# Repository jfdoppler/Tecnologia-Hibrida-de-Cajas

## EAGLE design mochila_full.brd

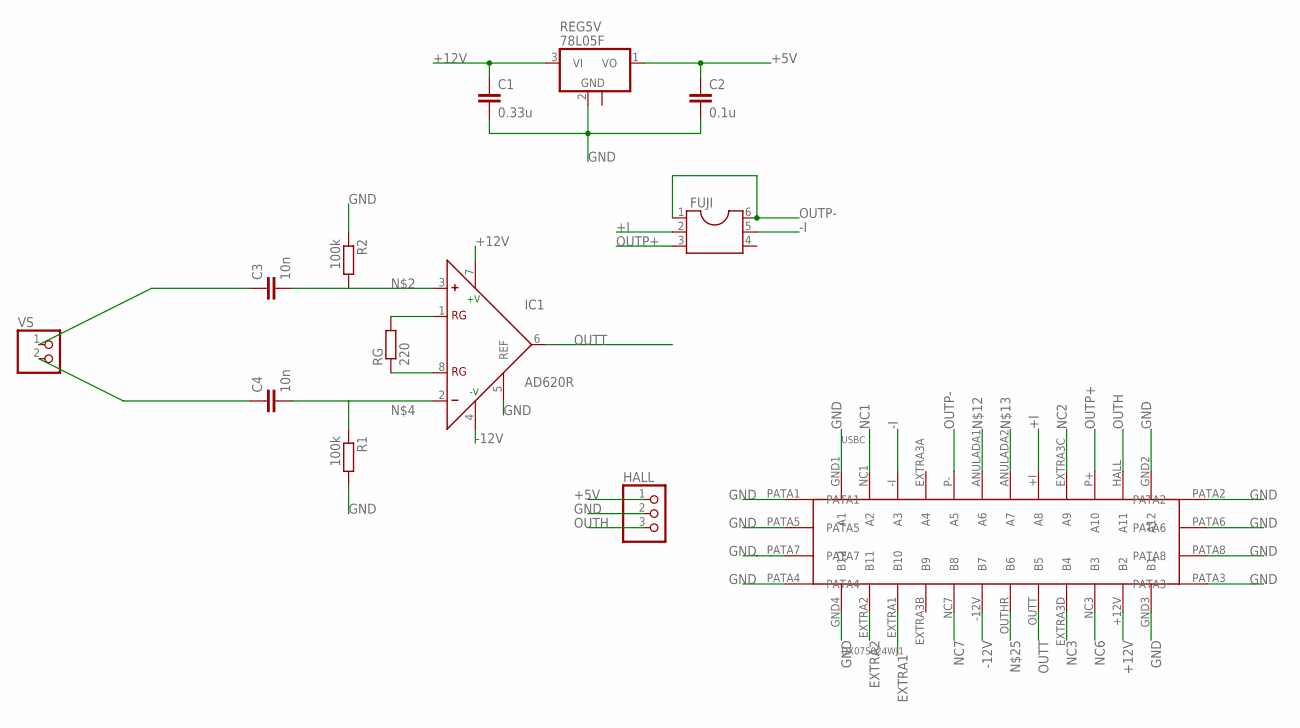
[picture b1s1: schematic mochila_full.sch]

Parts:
C1: 0.33u; C0805
C2: 0.1u; C0805
C3, C4: 10n; C0805
FUJI: DIL6; DIL06
HALL: PINHD-1X3; 1X03
IC1: AD620R; SO8
R1, R2: 100k; R0805
REG5V: 78L05F; SOT89
RG: 220; R0805
USBC: DX07S024WJ1
VS: PINHD-1X2; 1X02

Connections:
+5V: C2.1, HALL.1, REG5V.1 (VO)
+12V: C1.1, IC1.7 (+V), REG5V.3 (VI), USBC.+12V (B2)
+I: FUJI.2, USBC.+I (A8)
-12V: IC1.4 (-V), USBC.-12V (B7)
-I: FUJI.5, USBC.-I (A3)
EXTRA1: USBC.EXTRA1 (B10)
EXTRA2: USBC.EXTRA2 (B11)
GND: C1.2, C2.2, HALL.2, IC1.5 (REF), R1.2, R2.1, REG5V.2 (GND), USBC.GND1 (A1), USBC.GND2 (A12), USBC.GND3 (B1), USBC.GND4 (B12), USBC.PATA1, USBC.PATA2, USBC.PATA3, USBC.PATA4, USBC.PATA5, USBC.PATA6, USBC.PATA7, USBC.PATA8
unnamed: C3.1, VS.1
unnamed: C3.2, IC1.3 (+), R2.2
unnamed: C4.1, VS.2
unnamed: C4.2, IC1.2 (-), R1.1
unnamed: IC1.1 (RG), RG.2
unnamed: IC1.8 (RG), RG.1
NC1: USBC.NC1 (A2)
NC2: USBC.EXTRA3C (A9)
NC3: USBC.EXTRA3D (B4)
NC6: USBC.NC3 (B3)
NC7: USBC.NC7 (B8)
OUTH: HALL.3, USBC.HALL (A11)
OUTP+: FUJI.3, USBC.P+ (A10)
OUTP-: FUJI.1, FUJI.6, USBC.P- (A5)
OUTT: IC1.6 (OUT), USBC.OUTT (B5)

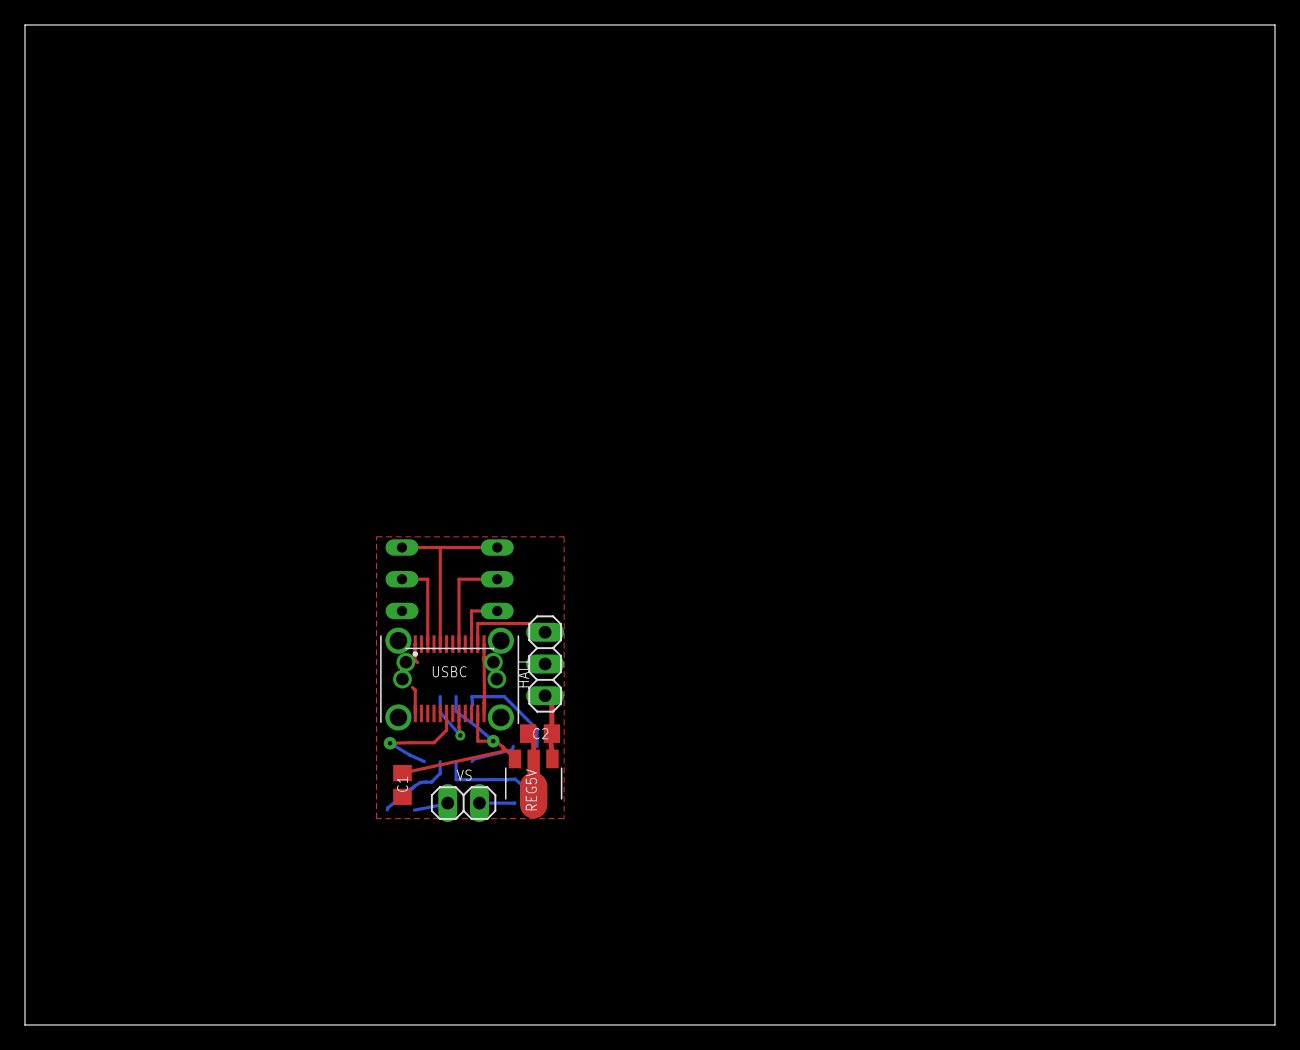
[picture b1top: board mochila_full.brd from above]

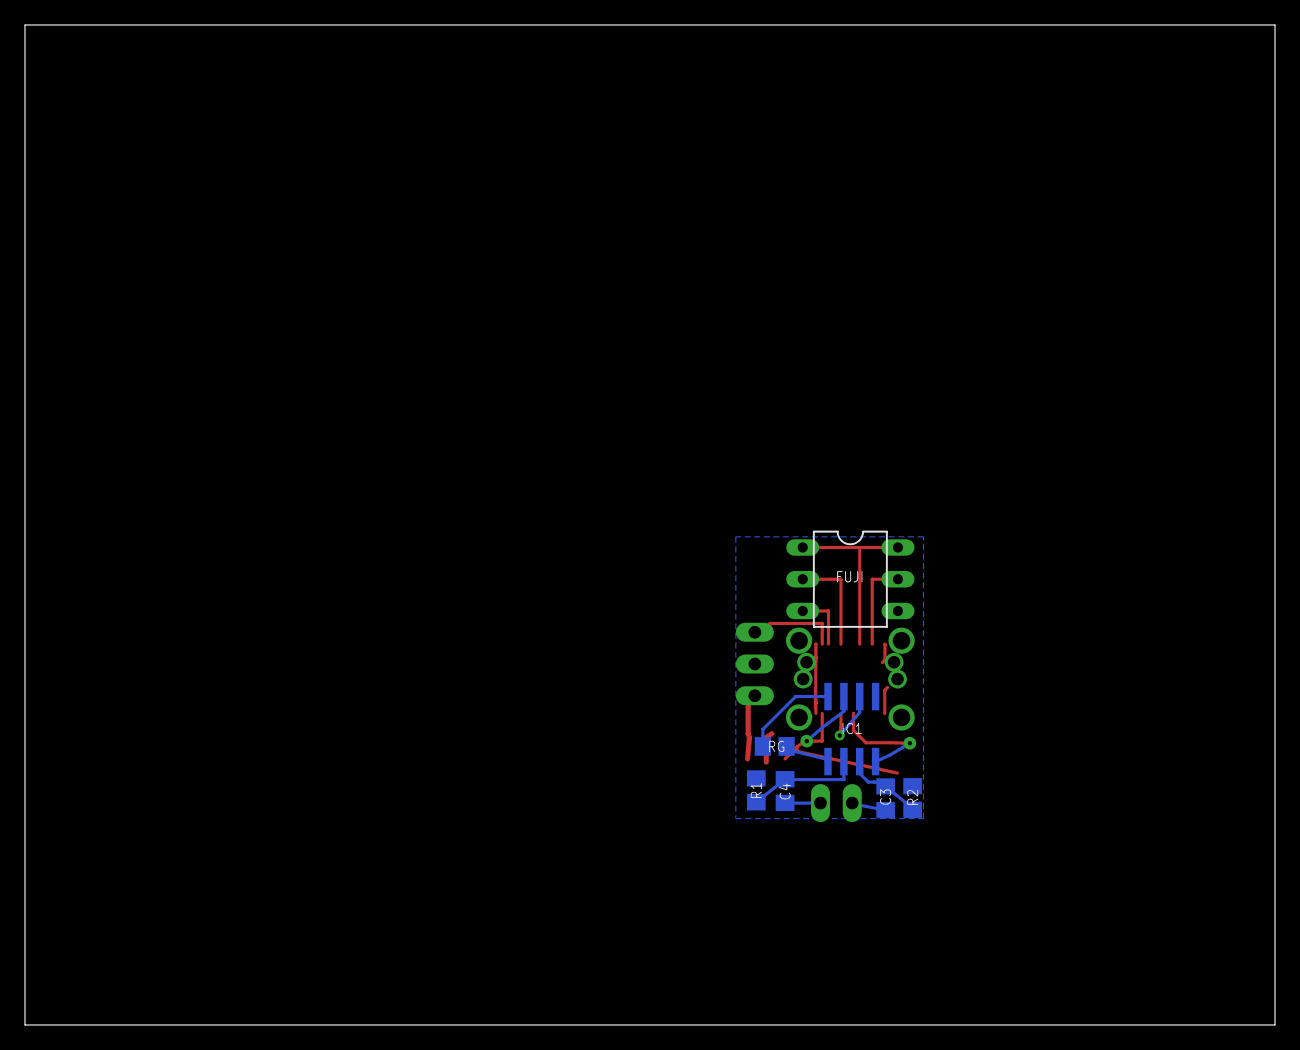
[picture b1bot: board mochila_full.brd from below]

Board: 2 copper layers, 100.0 x 80.0 mm, 13 parts (7 on the bottom side), 16 nets.

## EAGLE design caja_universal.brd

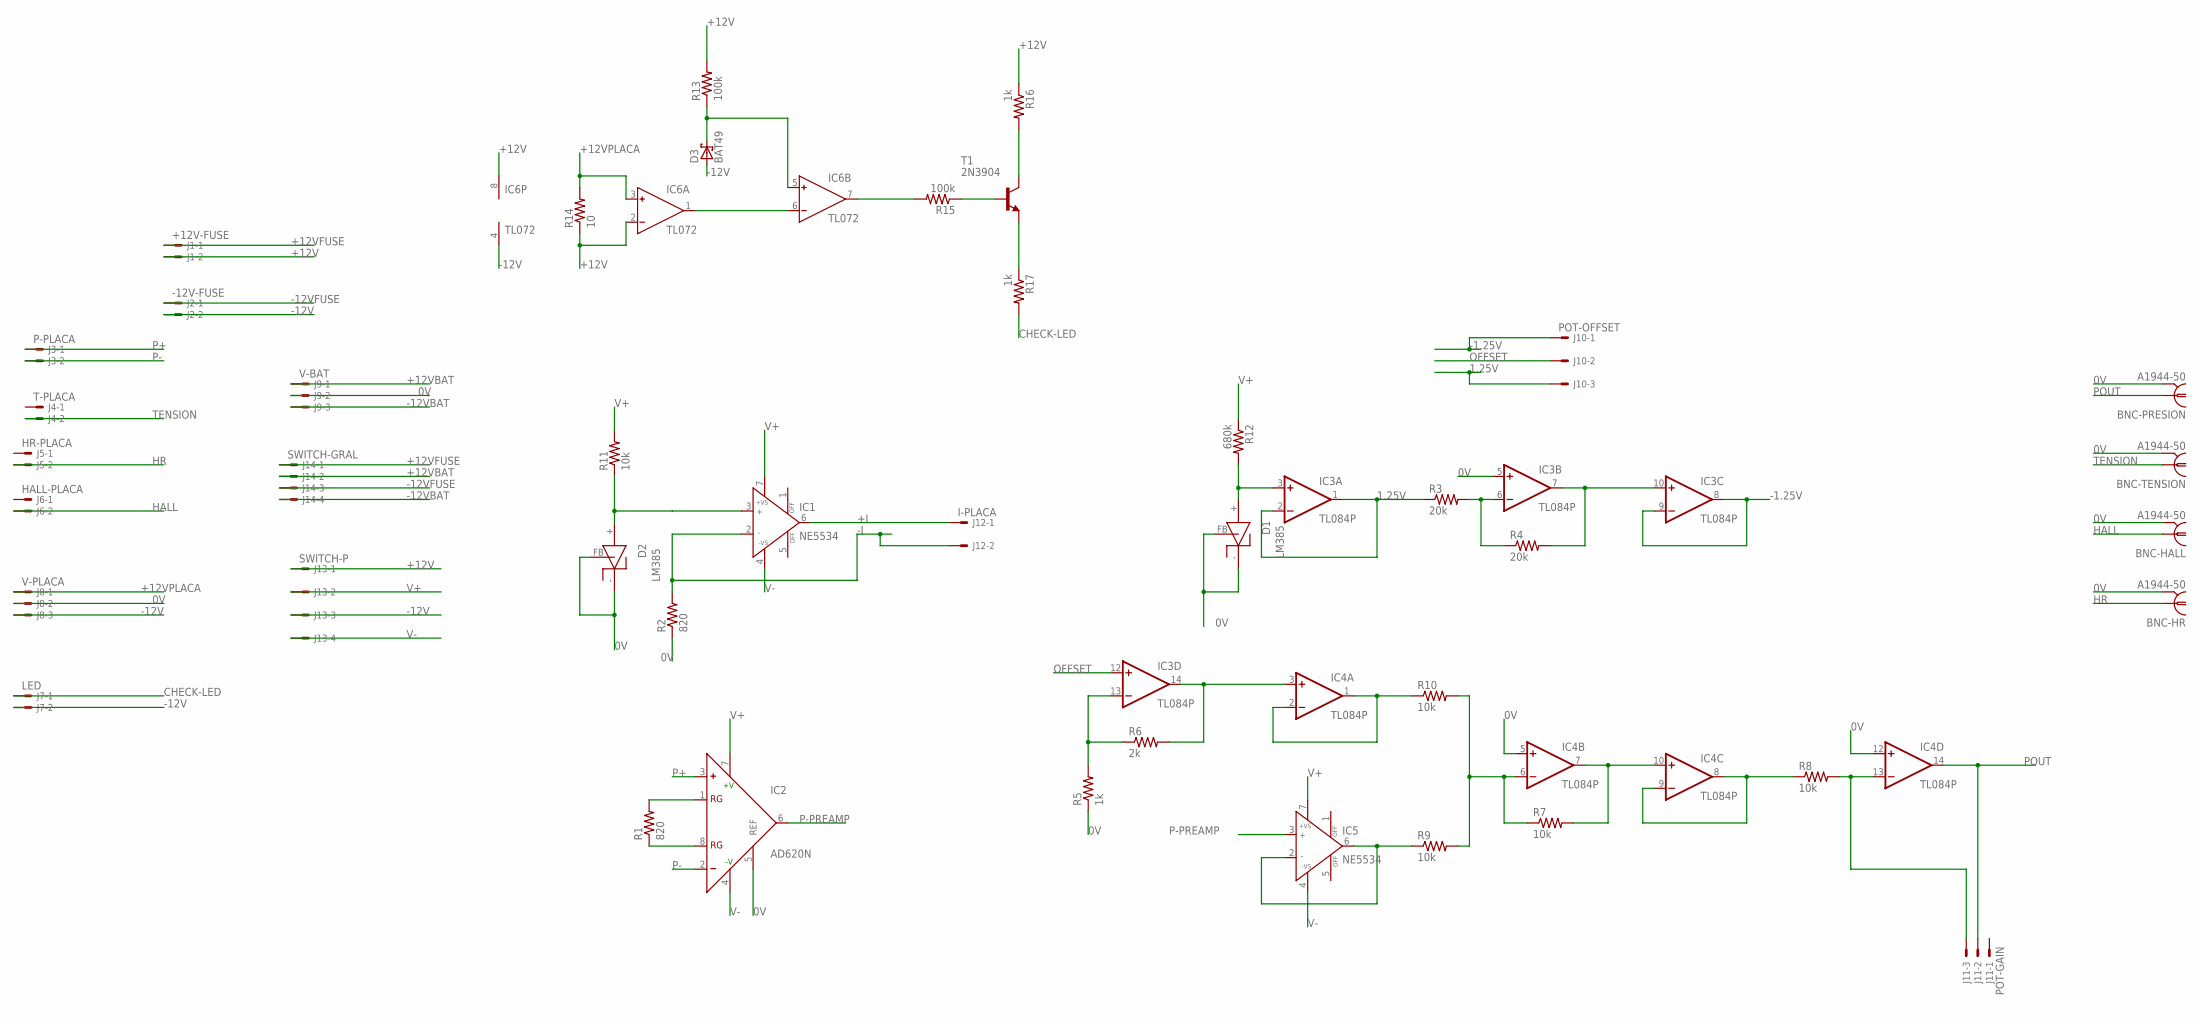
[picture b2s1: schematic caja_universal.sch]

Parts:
BNC-HALL: A1944-50; A1944
BNC-HR: A1944-50; A1944
BNC-PRESION: A1944-50; A1944
BNC-TENSION: A1944-50; A1944
D1, D2: LM385; TO-92
D3: BAT49; DO41-10
IC1, IC5: NE5534; DIL08
IC2: AD620N; DIL08
IC3, IC4: TL084P; DIL14
IC6: TL072; DIL08
J1: +12V-FUSE; 6410-02
J2: -12V-FUSE; 6410-02
J3: P-PLACA; 6410-02
J4: T-PLACA; 6410-02
J5: HR-PLACA; 6410-02
J6: HALL-PLACA; 6410-02
J7: LED; 6410-02
J8: V-PLACA; 6410-03
J9: V-BAT; 6410-03
J10: POT-OFFSET; 6410-03
J11: POT-GAIN; 6410-03
J12: I-PLACA; 6410-02
J13: SWITCH-P; 6410-04
J14: SWITCH-GRAL; 6410-04
R1, R2: 820; 0204/7
R3, R4: 20k; 0204/7
R5, R16, R17: 1k; 0204/7
R6: 2k; 0204/7
R7, R8, R9, R10, R11: 10k; 0204/7
R12: 680k; 0204/7
R13, R15: 100k; 0204/7
R14: 10; 0204/7
T1: 2N3904; TO92

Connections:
0V: BNC-HALL.2, BNC-HALL.3 (2), BNC-HALL.4 (2), BNC-HALL.5 (2), BNC-HR.2, BNC-HR.3 (2), BNC-HR.4 (2), BNC-HR.5 (2), BNC-PRESION.2, BNC-PRESION.3 (2), BNC-PRESION.4 (2), BNC-PRESION.5 (2), BNC-TENSION.2, BNC-TENSION.3 (2), BNC-TENSION.4 (2), BNC-TENSION.5 (2), D1.-, D1.FB, D2.-, D2.FB, IC2.5 (REF), IC3.5 (+IN), IC4.5 (+IN), IC4.12 (+IN), J8.2, J9.2, R2.1, R5.1
1.25V: IC3.1 (OUT), IC3.2 (-IN), J10.3, R3.1
+12V: IC6.2 (IN-), IC6.8 (V+), J1.2, J13.1, R13.2, R14.1, R16.1
+12VBAT: J9.1, J14.2
+12VFUSE: J1.1, J14.1
+12VPLACA: IC6.3 (IN+), J8.1, R14.2
+I: IC1.6 (OUT), J12.1
-1.25V: IC3.8 (OUT), IC3.9 (-IN), J10.1
-12V: D3.A, IC6.4 (V-), J2.2, J7.2, J8.3, J13.3
-12VBAT: J9.3, J14.4
-12VFUSE: J2.1, J14.3
-I: IC1.2 (IN-), J12.2, R2.2
CHECK-LED: J7.1, R17.2
HALL: BNC-HALL.1, J6.2
HR: BNC-HR.1, J5.2
unnamed: D2.+, IC1.3 (IN+), R11.1
unnamed: IC2.1 (RG), R1.2
unnamed: IC2.8 (RG), R1.1
unnamed: IC3.6 (-IN), R3.2, R4.1
unnamed: D1.+, IC3.3 (+IN), R12.2
unnamed: IC3.7 (OUT), IC3.10 (+IN), R4.2
unnamed: IC4.1 (OUT), IC4.2 (-IN), R10.1
unnamed: IC3.13 (-IN), R5.2, R6.1
unnamed: IC3.14 (OUT), IC4.3 (+IN), R6.2
unnamed: IC4.6 (-IN), R7.1, R9.2, R10.2
unnamed: IC5.2 (IN-), IC5.6 (OUT), R9.1
unnamed: IC4.7 (OUT), IC4.10 (+IN), R7.2
unnamed: IC4.8 (OUT), IC4.9 (-IN), R8.1
unnamed: IC4.13 (-IN), J11.3, R8.2
unnamed: R15.1, T1.2 (B)
unnamed: R16.2, T1.1 (C)
unnamed: R17.1, T1.3 (E)
unnamed: IC6.1 (OUT), IC6.6 (IN-)
unnamed: D3.C, IC6.5 (IN+), R13.1
unnamed: IC6.7 (OUT), R15.2
OFFSET: IC3.12 (+IN), J10.2
P+: IC2.3 (+), J3.1
P-: IC2.2 (-), J3.2
P-PREAMP: IC2.6 (OUT), IC5.3 (IN+)
POUT: BNC-PRESION.1, IC4.14 (OUT), J11.2
TENSION: BNC-TENSION.1, J4.2
V+: IC1.7 (+VS), IC2.7 (+V), IC3.4 (V+), IC4.4 (V+), IC5.7 (+VS), J13.2, R11.2, R12.1
V-: IC1.4 (-VS), IC2.4 (-V), IC3.11 (V-), IC4.11 (V-), IC5.4 (-VS), J13.4

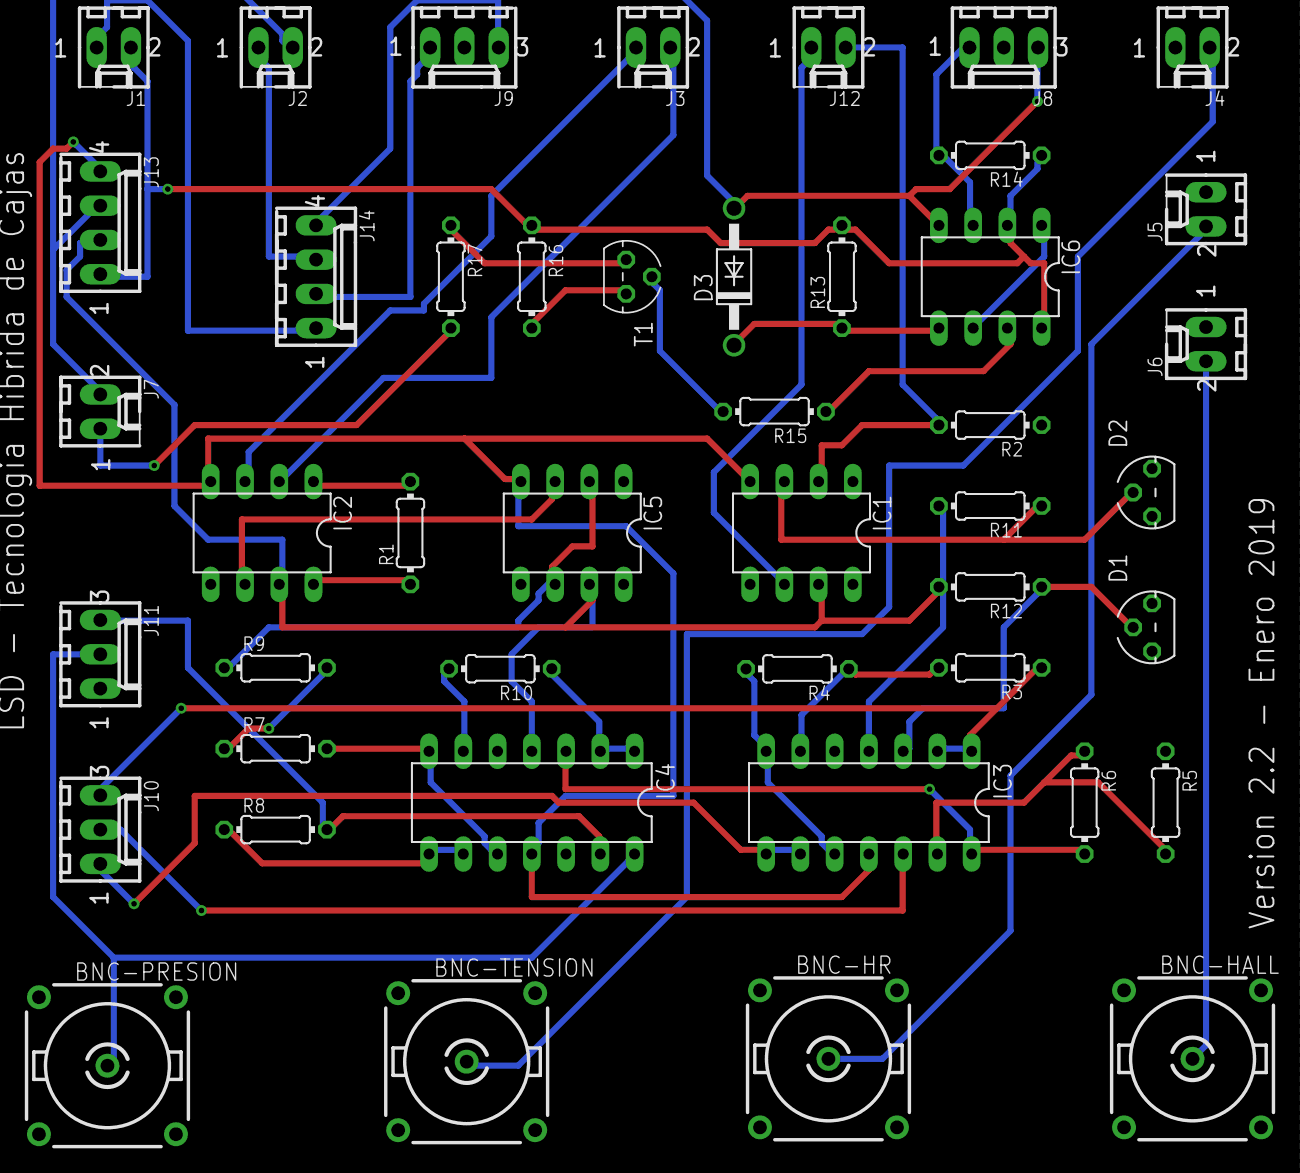
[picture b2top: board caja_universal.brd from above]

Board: 2 copper layers, 45 parts (0 on the bottom side), 43 nets.

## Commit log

2018-12-19 Commit inicial
2018-12-19 Esquematico finalizado (v0), board en progreso
2018-12-19 Avanzando...
2018-12-20 Terminada primera version de la placa
2018-12-26 Version para revisar (JyG)
2018-12-28 Agrego "mochila_full" (brd y sch) que es la primera version de la mochila para medir presion, tension y movimiento en simultaneo.
    ATENCION: para optimizar las rutas cambie casi todas las conexiones del conector usbc.
    FALTA: verificar y modificar la libreria del conector de manera acorde
2019-01-07 Agregamos con Juan uno GND que faltaban. Falta ver alimentacion de TL084 y cambiar valor resistencia del LED
2019-01-07 corregimos alimentacion TL084
2019-01-08 Corregimos placa de conexion universal y mochila
    Esta version se envia a imprimir
2019-01-09 Con nueva version de la libreria
2019-01-10 Cambios minimos caja, update libreria conector para mochila
2019-01-11 Modifico posicion de R3 y de la pista que lo une con el OPAM. Antes la pista pasaba debajo de un agujero para que pase el sostenedor del conector USBC.
2019-01-21 Usamos nueva libreria USBC
2019-01-22 Nuevo circuito de sense
    Agrego circuito diseñado por Gonza para no tener que usar los cables de check
2019-01-22 Version 2.1
    Smasheo todo para que los nombres y valores de todos los componentes queden visibles
    Cambio los nombres de los integrados para que sean los que usamos
2019-01-22 Corregidos valores circuito sense, potenciometro gain y cambio de libreria conectores. Agrego tRestrict alrededor de conectores para que las vias salgan siempre de bottom
2019-01-22 Agrego tRestrict alrededor de todos los zocalos
2019-01-22 Version para imprimir, routeada completa con tRestrict en zocalos y conectores
2019-01-22 Genero gerber files
2019-01-23 Version p/imprimir en masa
    Reemplazo los zener por regulador 78L05
    Agrego nombres y valores al layout
2019-01-23 Version para imprimir de la mochila, con gerbers generados en .zip
2019-01-23 Agrego los archivos de drill al zip
2019-01-24 Modifico para reducir tamaño debajo de 100x100 (precio impresion); genero gerbers nuevos: ENVIAR
2019-01-28 Agujeros de agarre del USB-C bien posicionados. No son agujeros, son PADS
2019-01-28 Gerbers finales(?)
2019-01-29 Agrego rectangulo en capa MEASURES para generar la capa profile en el Gerber
2019-05-10 Agrego datasheets
2019-05-10 Dejo de ignorar pdfs
2019-05-10 muevo datasheets
